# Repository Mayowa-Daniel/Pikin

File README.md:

# Pikin
A stick-less arcade controller.

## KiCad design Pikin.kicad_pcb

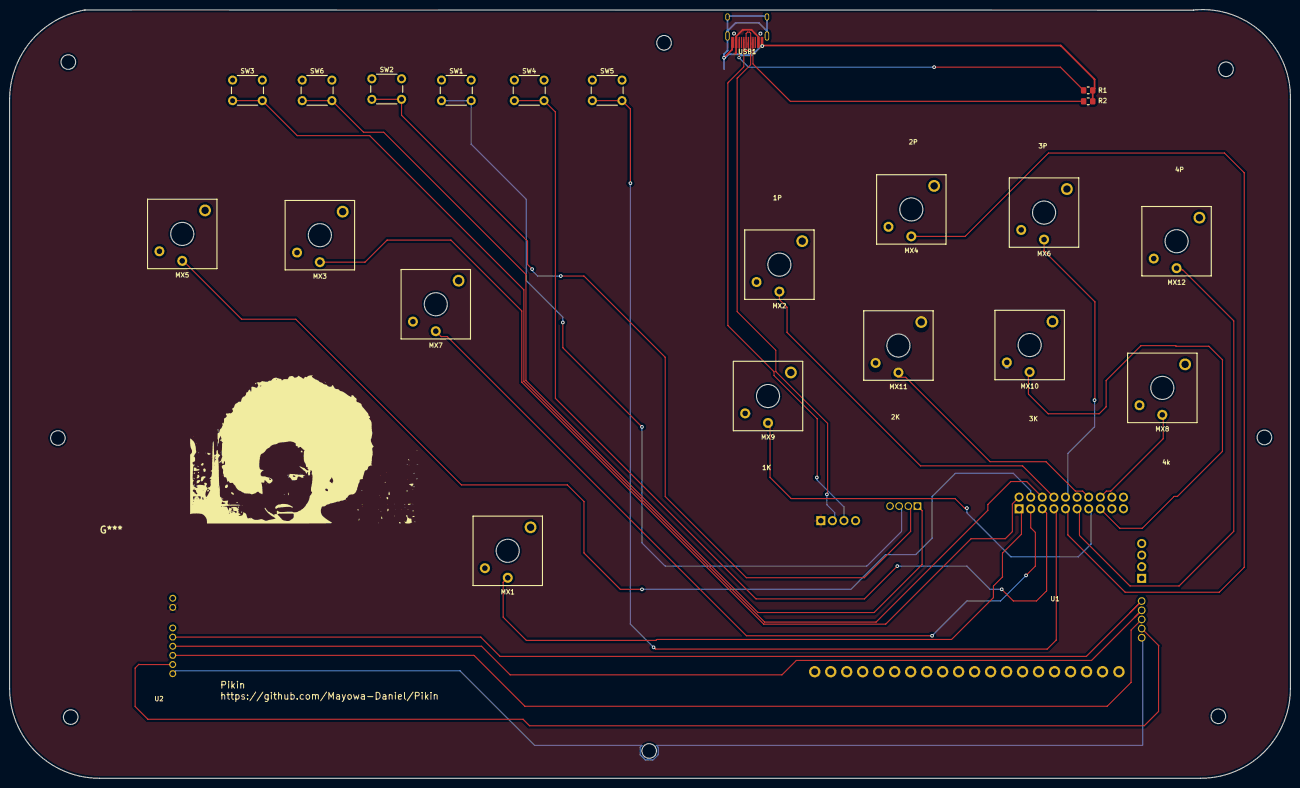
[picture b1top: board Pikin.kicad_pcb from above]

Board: 2 copper layers, 280.4 x 168.3 mm, 23 parts (0 on the bottom side), 29 nets.

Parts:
MX1, MX2, MX3, MX4, MX5, MX6, MX7, MX8, MX9, MX10, MX11, MX12: MX-NoLED; SW_Kailh_Choc_V2
R1, R2: 5.1k; R_0805_2012Metric_Pad1.20x1.40mm_HandSolder
SW1, SW2, SW3, SW4, SW5, SW6: SW_Push; SW_PUSH_6mm_H8.5mm
U1: brook_ufb; Brook_Universal_Fighting_Board
U2: UP5
USB1: HRO-TYPE-C-31-M-12; HRO-TYPE-C-31-M-12-HandSoldering

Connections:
1K: MX9.1 (COL), U1.7 (J9_19_1K/X/A)
1P: MX2.1 (COL), U1.14 (J9_20_1P/Square/X)
2K: MX11.1 (COL), U1.8 (J9_20_2K/O/B)
2P: MX4.1 (COL), U1.11 (J9_19_2P/Triangle/Y)
3K: MX10.1 (COL), U1.5 (J9_19_3K/R2/RT)
3P: MX6.1 (COL), U1.12 (J9_20_3P/R1/RB)
4K: MX8.1 (COL), U1.6 (J9_20_4K/L2/LT)
4P: MX12.1 (COL), U1.9 (J9_19_4P/L1/LB)
D+: U1.35 (J6-1_D+), USB1.6 (DP1), USB1.8 (DP2)
D-: U1.36 (J6-1_D-), USB1.5 (DN2), USB1.7 (DN1)
Down: MX3.1 (COL), U1.20 (J9_20_DOWN)
GND: MX1.2 (ROW), MX2.2 (ROW), MX3.2 (ROW), MX4.2 (ROW), MX5.2 (ROW), MX6.2 (ROW), MX7.2 (ROW), MX8.2 (ROW), MX9.2 (ROW), MX10.2 (ROW), MX11.2 (ROW), MX12.2 (ROW), R1.1, R2.2, SW1.1, SW2.1, SW3.1, SW4.1, SW5.1, SW6.1, U1.3 (J9_19_GND), U1.4 (J9_20_GND), U1.10 (J9_20_GND), U1.33 (J4_GND), U1.34 (J6-1_GND), U2.1, USB1.1 (GND), USB1.12 (GND), USB1.13 (SHIELD)
Home: SW3.2, U1.16 (J9_20_Home/Ps/Xb)
LSB: SW2.2, U1.31 (J4_LSB)
Left: MX5.1 (COL), U1.18 (J9_20_LEFT)
MOSI: U1.25 (J2_5), U2.4
unnamed: R1.2, USB1.10 (CC2)
unnamed: R2.1, USB1.4 (CC1)
RSB: SW1.2, U1.32 (J4_RSB)
Right: MX7.1 (COL), U1.17 (J9_19_RIGHT)
SCL: U1.27 (J2_3), U2.6
SDA: U1.26 (J2_4), U2.5
SS: U1.28 (J2_2), U2.7
Select: SW4.2, U1.15 (J9_19_Select/Share/Back)
Start: SW5.2, U1.13 (J9_19_Start/Options)
TouchPad: SW6.2, U1.30 (J4_TPKEY)
UGND: U1.29 (J2_1), U2.8
Up: MX1.1 (COL), U1.19 (J9_19_UP)
VCC: U1.37 (J6-1_VCC), U2.2, USB1.2 (VBUS), USB1.11 (VBUS)

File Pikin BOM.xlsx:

Comment | Designator | Footprint | JLCPCB Part #（optional）
MX-NoLED | MX1-MX12 | Switch_Keyboard_Kailh:SW_Kailh_Choc_V2
5.1k | R1, R2 | Resistor_SMD:R_0805_2012Metric_Pad1.20x1.40mm_HandSolder
SW_Push | SW1-SW6 | Button_Switch_THT:SW_PUSH_6mm_H8.5mm
brook_ufb | U1 | Brook_UFB:Brook_Universal_Fighting_Board
HRO-TYPE-C-31-M-12 | USB1 | Type-C:HRO-TYPE-C-31-M-12-HandSoldering | C165948

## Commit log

2022-05-18 Done
2023-01-12 Added image files for 3D board view and layout
